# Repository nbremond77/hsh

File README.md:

# hsh
Home Smart Home: The Internet of Things to make home a smart place.

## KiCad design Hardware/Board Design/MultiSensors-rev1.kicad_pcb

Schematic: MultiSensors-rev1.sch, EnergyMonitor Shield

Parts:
C1, C2, C3, C6, C7, C8: 10uF/50V; c_elec_6.3x7.7
C4: 10n; C_0805
C5: 100n; C_0805
C9, C10, C11: 10uF/50V; Capacitor10x21RM5
D1: LED; LED-1206
D2, D3: IR_LED; LED-5MM
D4, D5, D6: BAS40-04; Diode_SOT23
IC1: MAX3483; SOIC-8-W
IC2: RFM12B; RFM12
J1, J2: Jack_3.5mm_3pin; Jack_EBS35
J3: PowerInput; Pin_Header_Straight_1x02
J4, J6: UEXT; Pin_Header_Straight_2x05
J5: Outputs; Pin_Header_Straight_1x04
J7: Arduino_Uno_Header; ARDUINO_SHIELD
J8: Raspberry; Pin_Header_Straight_2x13
J9: Antenna; SMA
JP1: DMX R/W; Pin_Header_Straight_1x02
K1: RS485/DMX; Pin_Header_Straight_1x03
L1, L2: 4.7uH; INDUCTOR_V
P1, P2: ACin; Pin_Header_Straight_1x02
P3: PIR; Pin_Header_Straight_1x03
P4: DHT22; Pin_Header_Straight_1x04
P5, P6: 1_Wire; Pin_Header_Straight_1x03
Q2: 2N2222; TO-92-Bipolar-molded-wide-universal-EBC
R1, R6, R27, R28: NC; R_0805
R2, R5, R7, R10, R16: 100k; R_0805
R3, R8: 0R; R_0805
R4, R9: 22R; R_0805
R11, R34: 976k; R_0805
R12, R13, R15, R24: 1k; R_0805
R14: 470R; R_0805
R17: 50k; R_0805
R18: 100; R_0805
R19, R20, R23: 47; R_0805
R21: 100R; R_0805
R22, R35: 562k; R_0805
R25: 2k2; R_0805
R26: 4K7; R_0805
R29, R30: 680R; R_0805
R31: 120R; R_0805
R32: 47R; R_0805
R33: 10k; R_0805
SW1: Push1; SW_PUSH_SMALL
U1: TSOP_2438; TSOP2438
U2: MRF24J40MA; Mrf24J40MA
U3: Mcp1640t-i/chy; SOT-23-6
U4: MCP1640t-i/chy; SOT-23-6

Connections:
1Wire: J7.AD5, P4.3, P5.2 (PM), P6.2 (PM), R26.1
3V3: C4.2, C8.1, C11.1, D4.3 (K), D5.3 (K), D6.3 (K), IC2.9 (VDD), J7.3V3 (3.3V), J8.1, R27.2, R28.2, R33.1, R34.1, U2.10 (VCC), U4.5 (VOUT)
+3.3VADC: J7.AREF, R1.2, R2.2, R6.2, R7.2
+BATT: C6.1, C9.1, J3.2, L1.1, L2.1, R16.1, U3.6 (VIN), U4.3 (EN), U4.6 (VIN)
AGND: C1.2, C2.2, J7.GND3 (GND), R5.2, R10.2
AN0: D5.2 (KA), J7.AD1, R12.2
AN1: D4.2 (KA), J7.AD2, R13.2
AN2: D6.2 (KA), J7.AD0, R16.2, R17.1
GND: C3.2, C4.1, C5.2, C6.2, C7.2, C8.2, C9.2, C10.2, C11.2, D4.1 (A), D5.1 (A), D6.1 (A), IC1.5 (GND), IC2.7 (GND), IC2.10 (GND), J3.1, J4.2, J5.1, J6.2, J7.GND1 (GND), J7.GND2 (GND), J8.6, J9.2 (GND1), J9.3 (GND2), J9.4 (GND3), J9.5 (GND4), P3.1, P4.1, P5.1, P6.1, Q2.E, R17.2, R22.2, R25.1, R29.1, R32.2, R35.2, SW1.2, U1.3, U2.1 (GND), U2.11 (GND), U2.12 (GND), U3.2 (GND), U4.2 (GND)
INT: IC2.11 (~INT~/VDI), J7.2 (PWM2/2), U2.4 (INT)
IR_In: J7.AD3, U1.1
MISO: IC2.1 (SDO), J4.7, J6.7, J7.12 (PWM12/12), J7.SP1 (MISO), U2.7 (SDO)
MOSI: IC2.12 (SDI), J4.8, J6.8, J7.11 (PWM11/11), J7.SP4 (MOSI), U2.5 (SDI)
unnamed: C1.1, J1.1 (S), P1.1, R2.1, R4.1, R5.1
unnamed: C2.1, J2.1 (S), P2.1, R7.1, R9.1, R10.1
unnamed: C3.1, R21.2, U1.2
unnamed: D1.2 (K), R14.2
unnamed: D2.1 (A), R18.2
unnamed: D2.2 (K), D3.1 (A)
unnamed: D3.2 (K), Q2.C
unnamed: IC1.6 (A), K1.2, R30.2, R31.2
unnamed: IC1.7 (B), K1.1, R29.2, R31.1
unnamed: IC2.3 (FSK/DATA/nFFS), R33.2
unnamed: IC2.8 (ANT), J9.1 (RF)
unnamed: J1.2 (T), P1.2 (PM), R3.1
unnamed: J1.3 (R), R1.1
unnamed: J2.2 (T), P2.2 (PM), R8.1
unnamed: J2.3 (R), R6.1
unnamed: J5.2, R19.1
unnamed: J5.3, R20.1
unnamed: J8.8, R24.2
unnamed: J8.10, R23.2
unnamed: J8.11, JP1.2
unnamed: K1.3, R32.1
unnamed: L1.2, U3.1 (SW)
unnamed: L2.2, U4.1 (SW)
unnamed: Q2.B, R15.2
unnamed: R11.2, R22.1, U3.4 (VFB)
unnamed: R3.2, R4.2, R12.1
unnamed: R8.2, R9.2, R13.1
unnamed: R34.2, R35.1, U4.4 (VFB)
Out0: J7.6 (PWM6/6), R19.2
Out1: J7.5 (PWM5/5), R15.1, R20.2
PIR: J7.AD4, P3.2 (PM)
PowerOn: J7.9 (PWM9/9), U3.3 (EN)
Push1: J7.8 (PWM8/8), R14.1, SW1.1
RESET: IC2.6 (~RES), J7.SP5 (RESET), U2.2 (nRESET)
RTS1: IC1.2 (~RE), IC1.3 (DE), J7.3 (PWM3/3), JP1.1
Rx1: IC1.1 (RO), J4.4, J6.4, J7.0 (RX/URXD/0), R24.1, R25.2
SCK: IC2.13 (SCK), J4.9, J6.9, J7.13 (PWM13/13), J7.SP3 (SCK), U2.6 (SCK)
SCL: J4.5, J6.5, J7.SCL (SCL1/TWCK0), R27.1
SDA: J4.6, J6.6, J7.SDA (SDA1/TWD0), R28.1
SPI_CS0: IC2.14 (~SEL), J4.10, J7.10 (SS0/PWM10/ETH-CS/10), U2.8 (nCS)
SPI_CS1: J6.10, J7.4 (SS1/PWM4/SD-CS/4)
Tx1: IC1.4 (DI), J4.3, J6.3, J7.1 (TX/UTXD/1), R23.1
VDD: C5.1, C7.1, C10.1, D1.1 (A), IC1.8 (VCC), J4.1, J5.4, J6.1, P3.3, P4.4, P5.3, P6.3, R11.1, R18.1, R21.1, R26.2, R30.1, U3.5 (VOUT)
Wake: IC2.2 (~IRQ), J7.7 (PWM7/7), U2.3 (WAKE)

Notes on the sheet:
Radio Interface
RS485 / DMX interface 1
Outputs
User Interface
1-Wire Temperature Sensor
Relative Humidity Sensor
IR LED
IR Receiver
Extension UEXT
Zigbee (double implant)
Configurable Input 1
Configurable Input 0
Battery monitoring
PIR Sensor
Serial connection to Raspberry (5V)

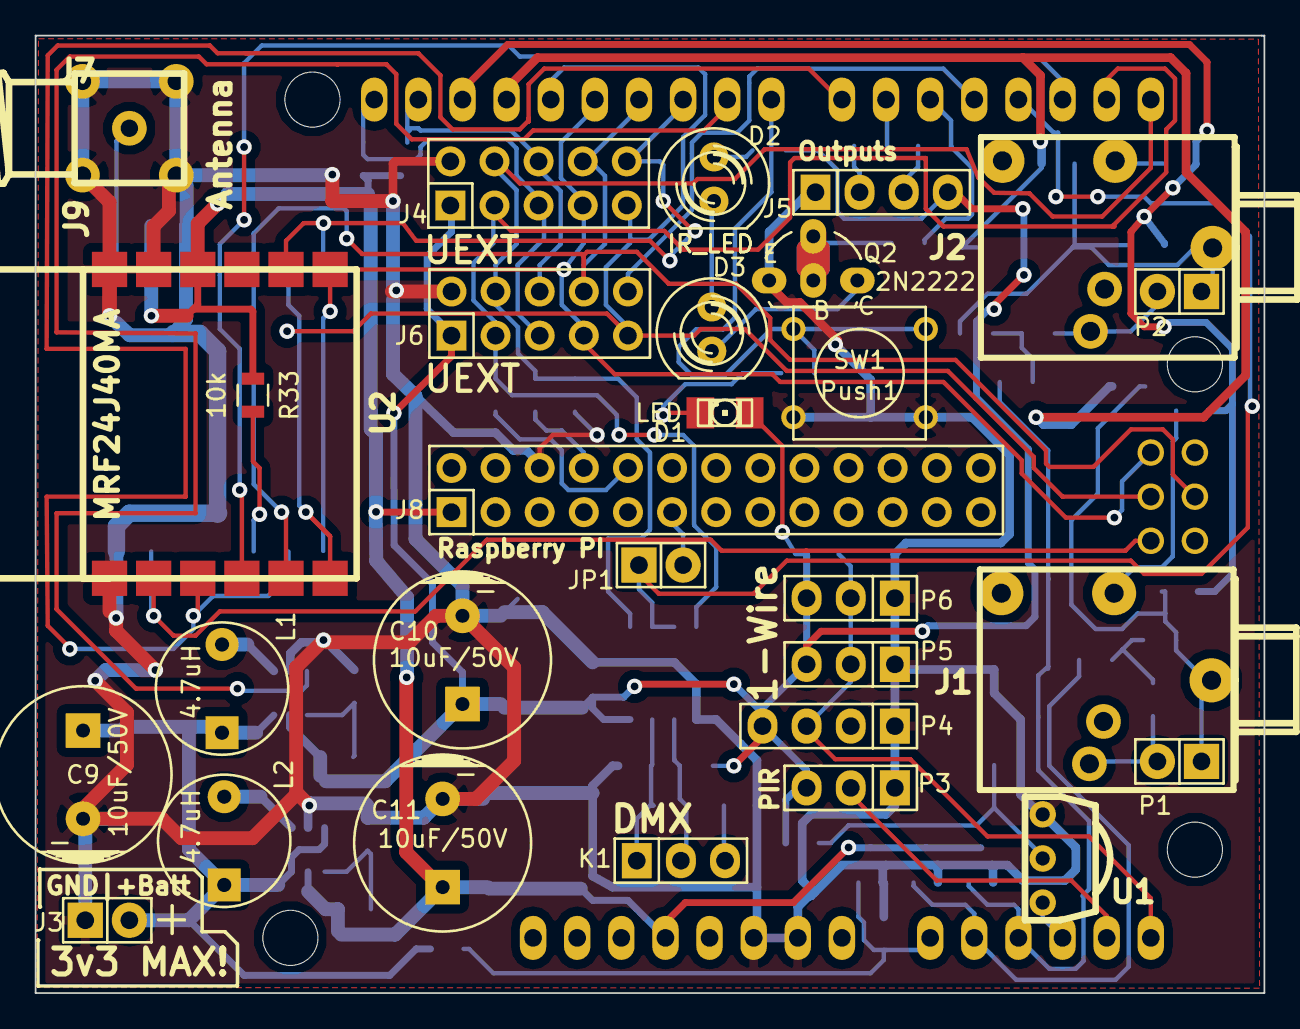
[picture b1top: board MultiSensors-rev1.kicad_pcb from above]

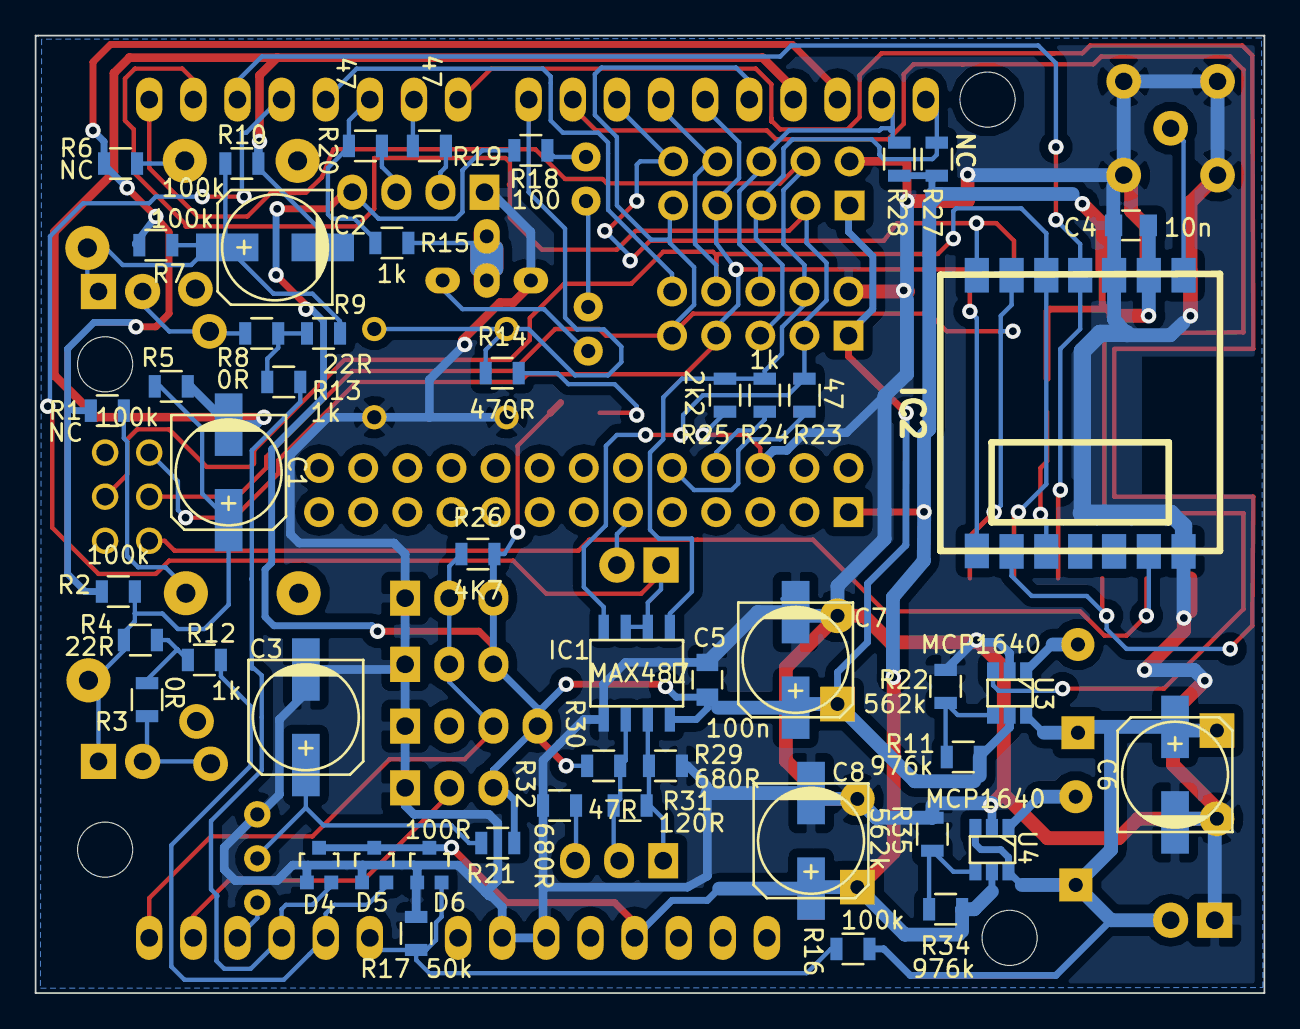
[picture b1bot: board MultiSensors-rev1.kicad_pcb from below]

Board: 2 copper layers, 70.7 x 55.1 mm, 79 parts (49 on the bottom side), 57 nets.

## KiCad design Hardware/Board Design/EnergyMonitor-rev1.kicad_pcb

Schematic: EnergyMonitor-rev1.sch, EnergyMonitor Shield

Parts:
C1, C2, C3, C4, C5, C6, C9, C10, C11, C12, C13, C14, C15: 10uF/50V; c_elec_6.3x7.7
C7: 1000uF/50V; Elko_vert_31.5x16mm_RM7.5
C8: 100n; C_1206
C16: 10n; C_0805
C17, C18: 100n; C_0805
D1: TVS_BIPOL; Diode_DO-41_SOD81_Horizontal_RM10
D2: BRIDGE; bridge_wob
D3, D4, D5, D6, D7, D8, D11, D12, D13, D14, D15, D16: BAS40-04; Diode_SOT23
D9, D10: IR_LED; LED-5MM
D17, D18: LED; LED-1206
IC2, IC3: MAX3483; SOIC-8-W
IC4: RFM12B; RFM12
J1, J2, J3, J4, J5, J6, J7, J8, J9, J10, J11, J12: Jack_3.5mm_3pin; Jack_EBS35
J13, J14, J16, J17: UEXT; Pin_Header_Straight_2x06
J15: Arduino_Due_Header; ARDUINO_MEGA_SHIELD
J18: Extension; Pin_Header_Straight_2x06
J19: BMP180 Pressure; Pin_Header_Straight_1x04
J20: Antenna; SMA
J21, J22: Analog; Pin_Header_Straight_1x08
JP1: JUMPER; Pin_Header_Straight_1x02
K1, K2: RS485/DMX; Pin_Header_Straight_1x03
P1, P2, P3, P4, P5, P6, P8, P9, P10, P11, P12, P13: ACin; Pin_Header_Straight_1x02
P7: CONN_2; Pin_Header_Straight_1x02
P14: Outputs; Pin_Header_Straight_2x05
P15: SRF05 Ultrasonic Level Sensor; Pin_Header_Straight_1x05
P16: DHT22; Pin_Header_Straight_1x04
P17, P18: 1_Wire; Pin_Header_Straight_1x03
Q1: 2N2222; TO-92-Bipolar-molded-wide-universal-EBC
R1: Polyswitch 1A; R3-5
R2, R7, R12, R17, R22, R27, R38, R39, R44, R45, R50, R51, R56, R57, R62, R63, R68, R69, R85, R101, R102: NC; R_0805
R3, R6, R8, R11, R13, R16, R18, R21, R23, R26, R28, R31, R40, R43, R46, R49, R52, R55, R58, R61, R64, R67, R70, R73: 100k; R_0805
R4, R9, R14, R19, R24, R29, R41, R47, R53, R59, R65, R71: 0R; R_0805
R5, R10, R15, R20, R25, R30, R42, R48, R54, R60, R66, R72: 22R; R_0805
R32, R33, R34, R35, R36, R37, R74, R76, R77, R78, R79, R80, R81: 1k; R_0805
R75: 100; R_0805
R82: 100R; R_0805
R83, R84: 470R; R_0805
R86, R87, R88, R92, R93, R94, R95, R96, R97, R98, R99, R100, R103, R104, R113: 10k; R_0805
R89: 4K7; R_0805
R105, R106, R107, R108: 680R; R_0805
R109, R110: 120R; R_0805
R111, R112: 47R; R_0805
SW1: Push1; SW_PUSH_SMALL
SW2: 4PST; Pin_Header_Straight_2x04
U1: TSOP_2438; TSOP2438
U2: ULN2803; DIP-18__300_ELL
U3: MRF24J40MA; Mrf24J40MA

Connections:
1Wire: J15.29 (PIN29), P17.2 (PM), P18.2 (PM), R89.1
3V3: C16.2, C17.1, C18.1, D3.3 (K), D4.3 (K), D5.3 (K), D6.3 (K), D7.3 (K), D8.3 (K), D11.3 (K), D12.3 (K), D13.3 (K), D14.3 (K), D15.3 (K), D16.3 (K), IC2.8 (VCC), IC3.8 (VCC), IC4.9 (VDD), J13.1, J14.1, J15.3V3 (3.3V), J16.1, J17.1, J18.11, J19.4, P16.1, P17.3, P18.3, R82.1, R85.2, R88.1, R89.2, R101.2, R102.2, R103.2, R104.2, R107.1, R108.1, R113.1, U3.10 (VCC)
+3.3VADC: J15.AREF, J21.1, R2.2, R3.2, R7.2, R8.2, R12.2, R13.2, R17.2, R18.2, R22.2, R23.2, R27.2, R28.2
+5V: J15.5V, J15.5V_4 (5V), J15.5V_5 (5V), J18.12, P15.5, R38.2, R44.2, R50.2, R56.2, R62.2, R68.2, R75.1
+8V: C7.1, C8.1, D2.4 (V-), J15.V_IN (VIN), P14.10, U2.10 (COM)
ADCRef: J22.8, R39.2, R40.2, R45.2, R46.2, R51.2, R52.2, R57.2, R58.2, R63.2, R64.2, R69.2, R70.2
AGND: C1.2, C2.2, C3.2, C4.2, C5.2, C6.2, J15.GND3 (GND), J21.8, R6.2, R11.2, R16.2, R21.2, R26.2, R31.2
AN0: D3.2 (KA), J15.AD0, R76.2
AN1: D4.2 (KA), J15.AD1, R77.2
AN2: D5.2 (KA), J15.AD2, R78.2
AN3: D8.2 (KA), J15.AD3, R79.2
AN4: D6.2 (KA), J15.AD4, R80.2
AN5: D7.2 (KA), J15.AD5, R81.2
AN6: J21.2, R32.2
AN7: J21.3, R33.2
AN8: J21.4, R34.2
AN9: J21.5, R35.2
AN10: J21.6, R36.2
AN11: J21.7, R37.2
BL: J13.11, J14.11, J15.13 (PWM13/13), J16.11, J17.11
Data: J15.39 (PIN39), P16.2, R88.2
Data0: J13.12, J15.34 (PIN34)
Data1: J14.12, J15.42 (PIN42)
Data2: J15.40 (PIN40), J16.12, R92.2
Data3: J15.24 (PIN24), J17.12
GND: C7.2, C8.2, C15.2, C16.1, C17.2, C18.2, D1.2 (K), D2.1 (V+), D3.1 (A), D4.1 (A), D5.1 (A), D6.1 (A), D7.1 (A), D8.1 (A), D11.1 (A), D12.1 (A), D13.1 (A), D14.1 (A), D15.1 (A), D16.1 (A), D17.2 (K), D18.2 (K), IC2.5 (GND), IC3.5 (GND), IC4.7 (GND), IC4.10 (GND), J13.2, J14.2, J15.GND1 (GND), J15.GND2 (GND), J16.2, J17.2, J18.1, J19.3, J20.2 (GND1), J20.3 (GND2), J20.4 (GND3), J20.5 (GND4), JP1.2, P14.1, P15.1, P16.4, P17.1, P18.1, Q1.E, R87.1, R105.1, R106.1, R111.2, R112.2, SW1.2, SW2.1, SW2.3, SW2.5, SW2.7, U1.3, U2.9 (GND), U3.1 (GND), U3.11 (GND), U3.12 (GND); also elsewhere on the board
GNDRef: C9.2, C10.2, C11.2, C12.2, C13.2, C14.2, J22.1, R43.2, R49.2, R55.2, R61.2, R67.2, R73.2
INT: IC4.11 (~INT~/VDI), J15.AD13 (DAC1), U3.4 (INT)
IR_In: J15.AD14 (CANRX0), U1.1
IR_Out: J15.2 (PWM2/2), R74.1
In0: J15.51 (PIN51), R100.2
In1: J15.50 (PIN50), R99.2
In2: J15.49 (PIN49), R98.2
In3: J15.48 (PIN48), R97.2
In4: J15.47 (PIN47), R96.2
In5: J15.46 (PIN46), R95.2
In6: J15.45 (PIN45), R94.2
In7: J15.44 (PIN44), R93.2
LED1: J15.41 (PIN41), R84.2
LED2: J15.AD15 (CANTX1), R83.2
MISO: IC4.1 (SDO), J13.7, J14.7, J15.SP1 (MISO), J16.7, J17.7, U3.7 (SDO)
MOSI: IC4.12 (SDI), J13.8, J14.8, J15.SP4 (MOSI), J16.8, J17.8, U3.5 (SDI)
unnamed: C1.1, J1.1 (S), P1.1, R3.1, R5.1, R6.1
unnamed: C2.1, J2.1 (S), P2.1, R8.1, R10.1, R11.1
unnamed: C3.1, J3.1 (S), P3.1, R13.1, R15.1, R16.1
unnamed: C4.1, J4.1 (S), P4.1, R18.1, R20.1, R21.1
unnamed: C5.1, J5.1 (S), P5.1, R23.1, R25.1, R26.1
unnamed: C6.1, J6.1 (S), P6.1, R28.1, R30.1, R31.1
unnamed: C9.1, J7.1 (S), P8.1, R40.1, R42.1, R43.1
unnamed: C10.1, J8.1 (S), P9.1, R46.1, R48.1, R49.1
unnamed: C11.1, J9.1 (S), P10.1, R52.1, R54.1, R55.1
unnamed: C12.1, J10.1 (S), P11.1, R58.1, R60.1, R61.1
unnamed: C13.1, J11.1 (S), P12.1, R64.1, R66.1, R67.1
unnamed: C14.1, J12.1 (S), P13.1, R70.1, R72.1, R73.1
unnamed 54: C15.1, R82.2, U1.2; also elsewhere on the board
unnamed: D1.1 (A), P7.2 (PM), R1.2
unnamed: D2.2 (~1), P7.1
unnamed: D2.3 (~2), R1.1
unnamed: D9.1 (A), R75.2
unnamed: D9.2 (K), D10.1 (A)
unnamed: D10.2 (K), Q1.C
unnamed: D11.2 (KA), J15.AD6, J22.7
unnamed: D12.2 (KA), J15.AD7, J22.6
unnamed: D13.2 (KA), J15.AD8, J22.5
unnamed: D14.2 (KA), J15.AD9, J22.4
unnamed: D15.2 (KA), J15.AD10, J22.3
unnamed: D16.2 (KA), J15.AD11 (AD11/TXD3), J22.2
unnamed: D17.1 (A), R83.1
unnamed: D18.1 (A), R84.1
unnamed: IC2.6 (A), K1.2, R107.2, R109.2
unnamed: IC2.7 (B), K1.1, R105.2, R109.1
unnamed: IC3.6 (A), K2.2, R108.2, R110.2
unnamed: IC3.7 (B), K2.1, R106.2, R110.1
unnamed: IC4.3 (FSK/DATA/nFFS), R113.2
unnamed: IC4.8 (ANT), J20.1 (RF)
unnamed: J1.2 (T), P1.2 (PM), R4.1
unnamed: J1.3 (R), R2.1
unnamed: J2.2 (T), P2.2 (PM), R9.1
unnamed: J2.3 (R), R7.1
unnamed: J3.2 (T), P3.2 (PM), R14.1
unnamed: J3.3 (R), R12.1
unnamed: J4.2 (T), P4.2 (PM), R19.1
unnamed: J4.3 (R), R17.1
unnamed: J5.2 (T), P5.2 (PM), R24.1
unnamed: J5.3 (R), R22.1
unnamed: J6.2 (T), P6.2 (PM), R29.1
unnamed: J6.3 (R), R27.1
unnamed: J7.2 (T), P8.2 (PM), R41.1
unnamed: J7.3 (R), R38.1, R39.1
unnamed: J8.2 (T), P9.2 (PM), R47.1
unnamed: J8.3 (R), R44.1, R45.1
unnamed: J9.2 (T), P10.2 (PM), R53.1
unnamed: J9.3 (R), R50.1, R51.1
unnamed: J10.2 (T), P11.2 (PM), R59.1
unnamed: J10.3 (R), R56.1, R57.1
unnamed: J11.2 (T), P12.2 (PM), R65.1
unnamed: J11.3 (R), R62.1, R63.1
unnamed: J12.2 (T), P13.2 (PM), R71.1
unnamed: J12.3 (R), R68.1, R69.1
unnamed: J15.26 (PIN26), SW2.2
unnamed: J15.28 (PIN28), SW2.4
unnamed: J15.30 (PIN30), SW2.6
unnamed: J15.32 (PIN32), SW2.8
unnamed: J18.2, R100.1
unnamed: J18.3, R99.1
unnamed: J18.4, R98.1
unnamed: J18.5, R97.1
unnamed: J18.6, R96.1
unnamed: J18.7, R95.1
unnamed: J18.8, R94.1
unnamed: J18.9, R93.1
unnamed: J18.10, R92.1
unnamed: JP1.1, P15.2
unnamed: K1.3, R111.1
unnamed: K2.3, R112.1
unnamed: P14.2, U2.18 (1C)
unnamed: P14.3, U2.17 (2C)
unnamed: P14.4, U2.16 (3C)
unnamed: P14.5, U2.15 (4C)
unnamed: P14.6, U2.14 (5C)
unnamed: P14.7, U2.13 (6C)
unnamed: P14.8, U2.12 (7C)
unnamed: P14.9, U2.11 (8C)
unnamed: P15.4, R86.2
unnamed: Q1.B, R74.2
unnamed: R9.2, R10.2, R33.1
unnamed: R14.2, R15.2, R34.1
unnamed: R19.2, R20.2, R35.1
unnamed: R24.2, R25.2, R36.1
unnamed: R29.2, R30.2, R37.1
unnamed: R4.2, R5.2, R32.1
unnamed: R41.2, R42.2, R76.1
unnamed: R47.2, R48.2, R77.1
unnamed: R53.2, R54.2, R78.1
unnamed: R59.2, R60.2, R79.1
unnamed: R65.2, R66.2, R80.1
unnamed: R71.2, R72.2, R81.1
Out0: J15.3 (PWM3/3), U2.1 (1B)
Out1: J15.5 (PWM5/5), U2.2 (2B)
Out2: J15.6 (PWM6/6), U2.3 (3B)
Out3: J15.7 (PWM7/7), U2.4 (4B)
Out4: J15.8 (PWM8/8), U2.5 (5B)
Out5: J15.9 (PWM9/9), U2.6 (6B)
Out6: J15.11 (PWM11/11), U2.7 (7B)
Out7: J15.12 (PWM12/12), U2.8 (8B)
Push1: J15.43 (PIN43), R85.1, SW1.1
RESET: IC4.6 (~RES), J15.SP5 (RESET), U3.2 (nRESET)
RTS1: IC2.2 (~RE), IC2.3 (DE), J15.23 (PIN23)
RTS2: IC3.2 (~RE), IC3.3 (DE), J15.25 (PIN25)
Rx0: J13.4, J14.4, J15.0 (RX/URXD/0)
Rx1: IC2.1 (RO), J15.17 (RXD1/17)
Rx2: IC3.1 (RO), J15.19 (RXD2/19)
Rx3: J15.15 (RXD0/15), J16.4, J17.4
SCK: IC4.13 (SCK), J13.9, J14.9, J15.SP3 (SCK), J16.9, J17.9, U3.6 (SCK)
SCL: J15.21 (SCL0-3/TWCK1/AD13/21), J16.5, J17.5, J19.2, R101.1
SCL1: J13.5, J14.5, J15.SCL (SCL1/TWCK0), R103.1
SDA: J15.20 (SDA0-3/TWD1/AD12/20), J16.6, J17.6, J19.1, R102.1
SDA1: J13.6, J14.6, J15.SDA (SDA1/TWD0), R104.1
SPI_CS0: J13.10, J15.10 (SS0/PWM10/ETH-CS/10)
SPI_CS1: J14.10, J15.38 (PIN38)
SPI_CS2: IC4.14 (~SEL), J15.52 (PIN52/AD14/RXD3), J16.10, U3.8 (nCS)
SPI_CS3: J15.4 (SS1/PWM4/SD-CS/4), J17.10
Tx0: J13.3, J14.3, J15.1 (TX/UTXD/1)
Tx1: IC2.4 (DI), J15.16 (TXD1/16)
Tx2: IC3.4 (DI), J15.18 (TXD2/18)
Tx3: J15.14 (TXD0/14), J16.3, J17.3
US_Echo: J15.37 (PIN37), R86.1, R87.2
US_Trig: J15.35 (PIN35), P15.3
Wake: IC4.2 (~IRQ), J15.AD12 (DAC0/CANRX1), U3.3 (WAKE)

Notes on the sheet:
Configurable Input 0
Radio Interface
RS485 / DMX interface 2
RS485 / DMX interface 1
Outputs
User Interface
1-Wire Temperature Sensor
Relative Humidity Sensor
Configurable Input 1
Configurable Input 2
Configurable Input 3
Configurable Input 4
Configurable Input 5
Configurable Input 6
Configurable Input 7
Configurable Input 8
Configurable Input 9
Configurable Input 10
Configurable Input 11
Level Sensor
IR LED
Pressure Sensor
IR Receiver
Extension UEXT
Inputs Extension
Zigbee (double implant)

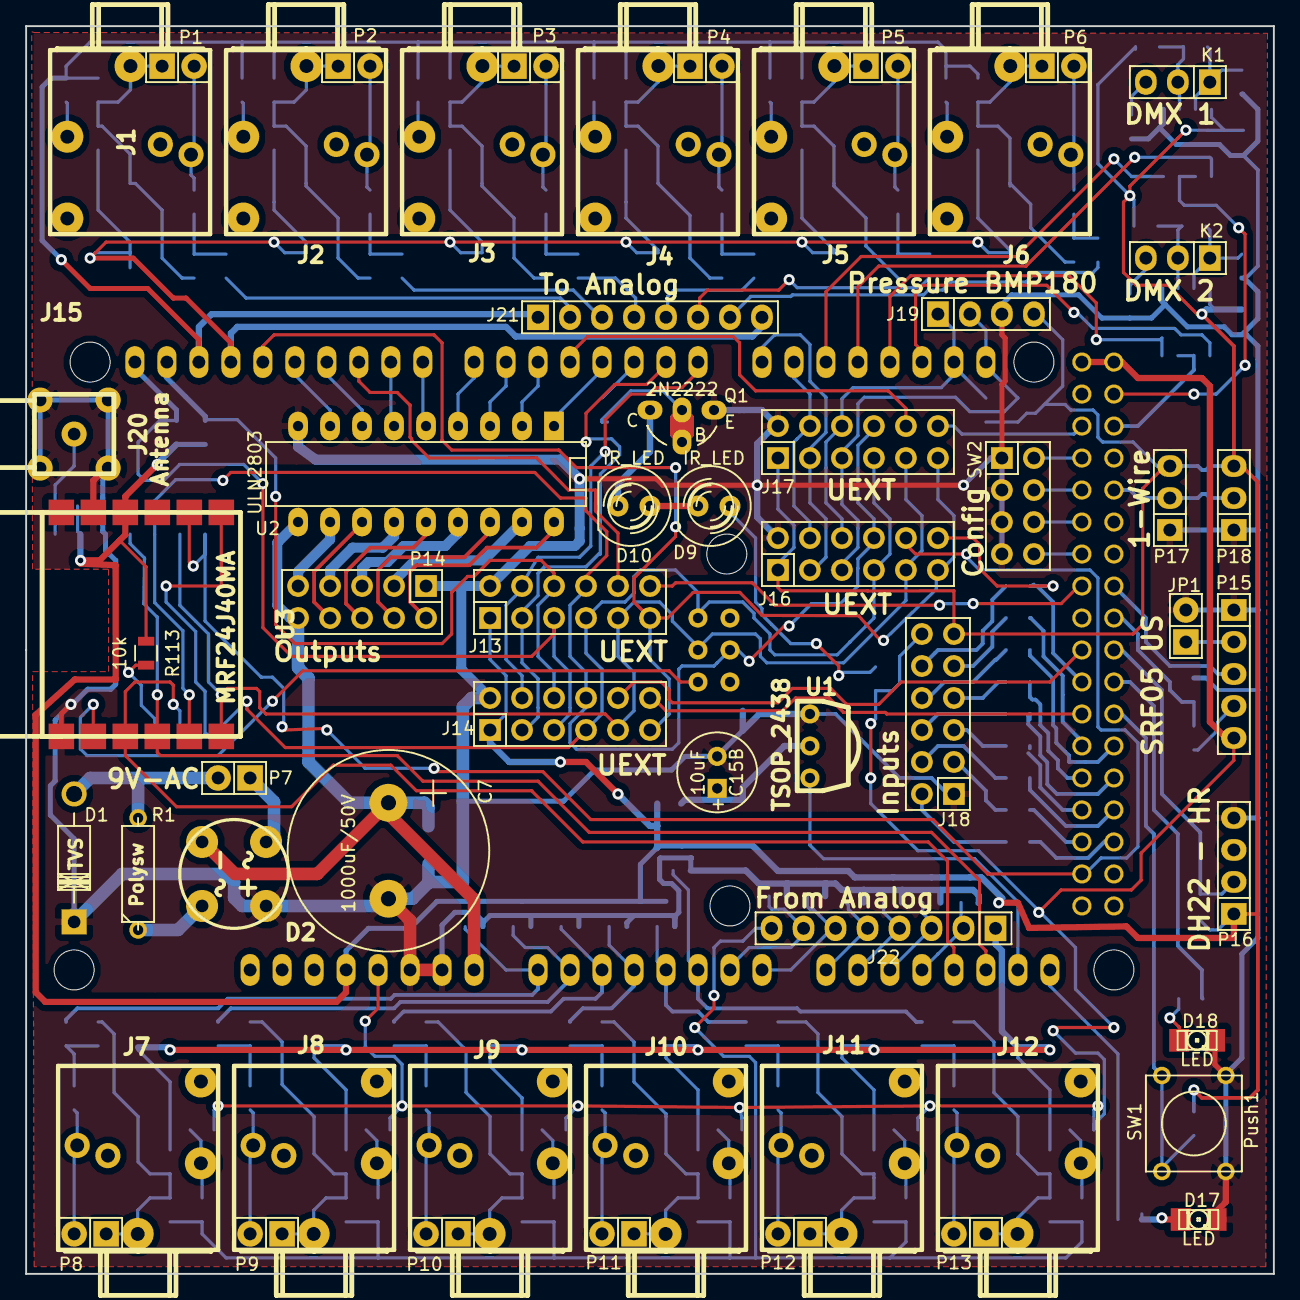
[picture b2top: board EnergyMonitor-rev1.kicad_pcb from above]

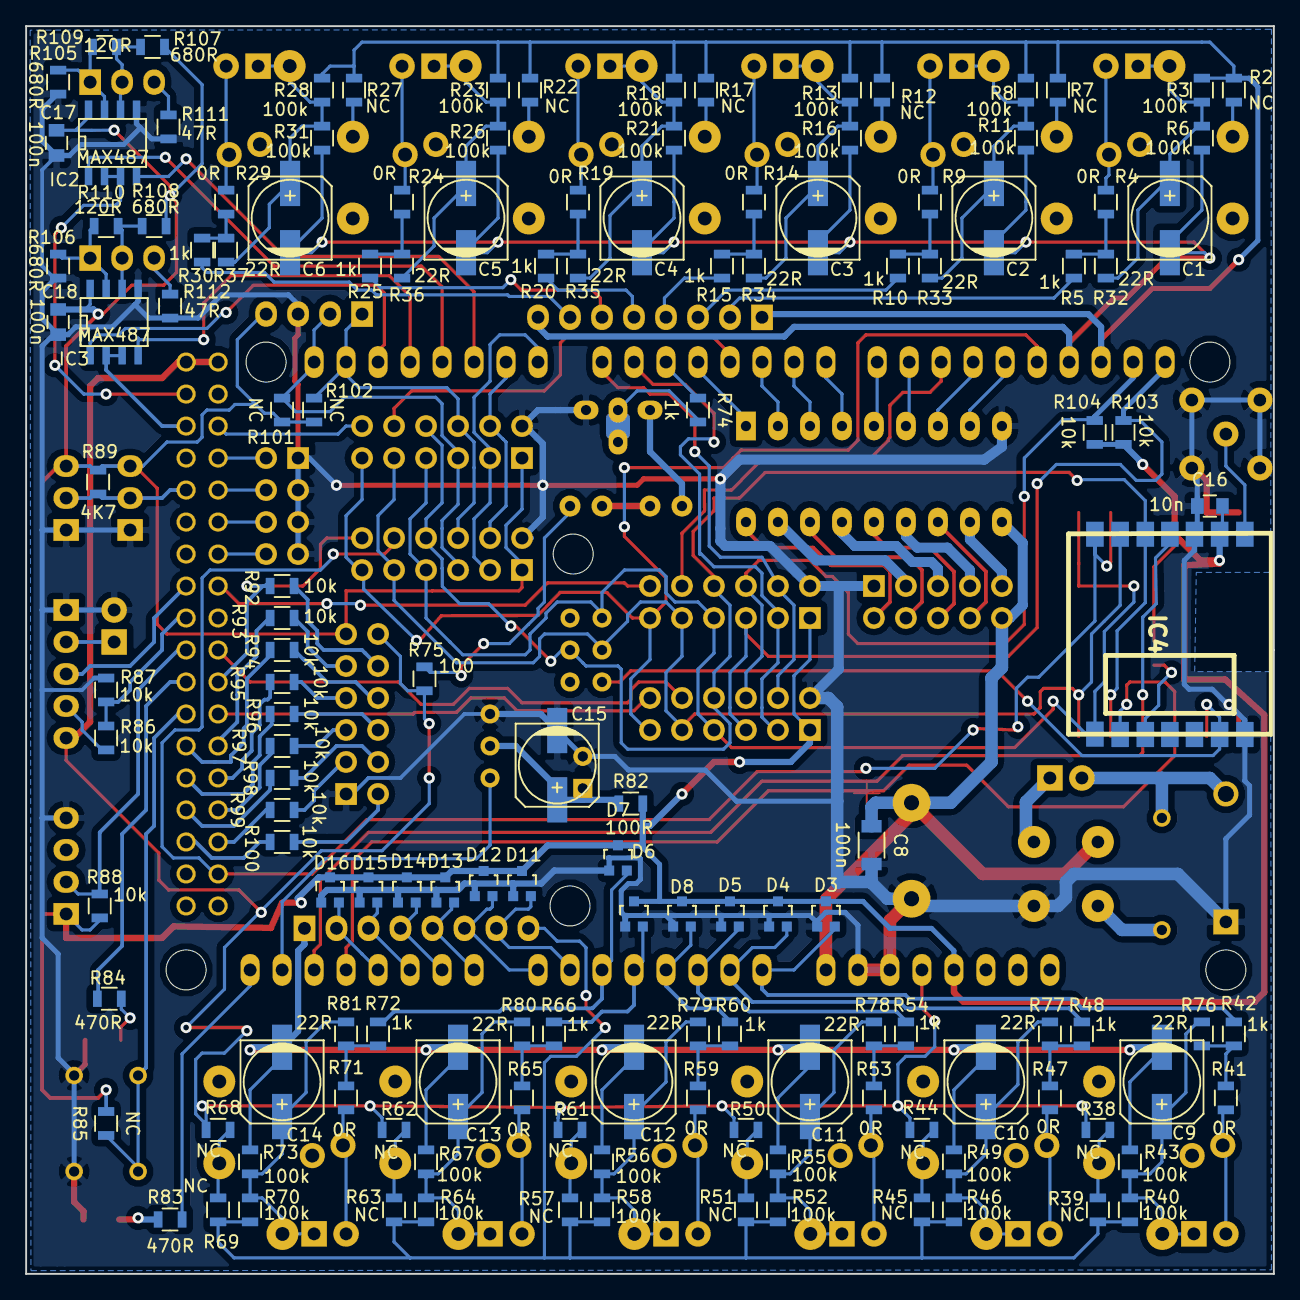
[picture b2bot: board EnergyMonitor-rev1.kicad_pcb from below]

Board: 2 copper layers, 99.1 x 99.1 mm, 200 parts (141 on the bottom side), 169 nets.

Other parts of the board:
C15B: 10uF; C1V7

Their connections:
GND: C15B.2; also elsewhere on the board
unnamed 54: C15B.1; also elsewhere on the board

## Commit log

2015-01-18 nouveau fichier : Datasheet/Arduino - ArduinoBoardDue.pdf nouveau fichier : Datasheet/Arduino - PinMappingSAM3X.pdf nouveau fichier : Datasheet/Arduino Due 2012 R3 ARM Version Main Control Board Best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
2015-01-18 nouveau fichier : Documentation/Schematic/EnergyMonitor-rev1.pdf nouveau fichier : Documentation/Schematic/MultiSensors-rev1.pdf
2015-01-18 nouveau fichier : 3D/EnergyMonitor-rev1_1.png nouveau fichier : 3D/EnergyMonitor-rev1_1_2.png nouveau fichier : 3D/EnergyMonitor-rev1_3.png nouveau fichier : 3D/EnergyMonitor-rev1_4.png
2015-01-18 Create gh-pages branch via GitHub
2015-01-20 nouveau fichier : Documentation/Architecture - rev 1.gif nouveau fichier : Documentation/Architecture - rev 1.odg nouveau fichier : Documentation/Architecture - rev 1.pdf nouveau fichier : Documentat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

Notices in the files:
Hardware/Board Design/EnergyMonitor-rev1.sch:
Open hardware Licence
